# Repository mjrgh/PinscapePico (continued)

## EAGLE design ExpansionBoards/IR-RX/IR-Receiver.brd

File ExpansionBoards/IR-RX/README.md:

# IR Receiver Satellite Board for Pinscape Pico

This is a small satellite board for the Pinscape Pico expansion
boards (both the DIY-friendly and "Pro" boards), which hosts the IR
Receiver sensor that allows Pinscape to receive signals from IR remote
controls. 

The IR sensor is deliberately separated from the main board so that it
can be positioned where it can receive line-of-sight IR transmissions
from remote controls.  The main Pinscape boards are probably going to
be hidden inside your pinball cabinet, so it doesn't make sense to
position the IR receiver directly on those boards.  Instead, you'll
probably want to place the IR receiver somewhere either outside the
cabinet, or in an opening in the cabinet where it has a view of the
exterior.  For example, you could place it behind a small hole drilled
in your speaker panel, or in the front wall of the cabinet body.

There are two versions of the board: a DIY-friendly version that uses
through-hole parts, and a version using surface-mount parts.  The
versions are functionally identical, and both versions work with the
Pinscape DIY-Friendly and "Pro" SMD expansion boards.  All of them use
the same connectors.

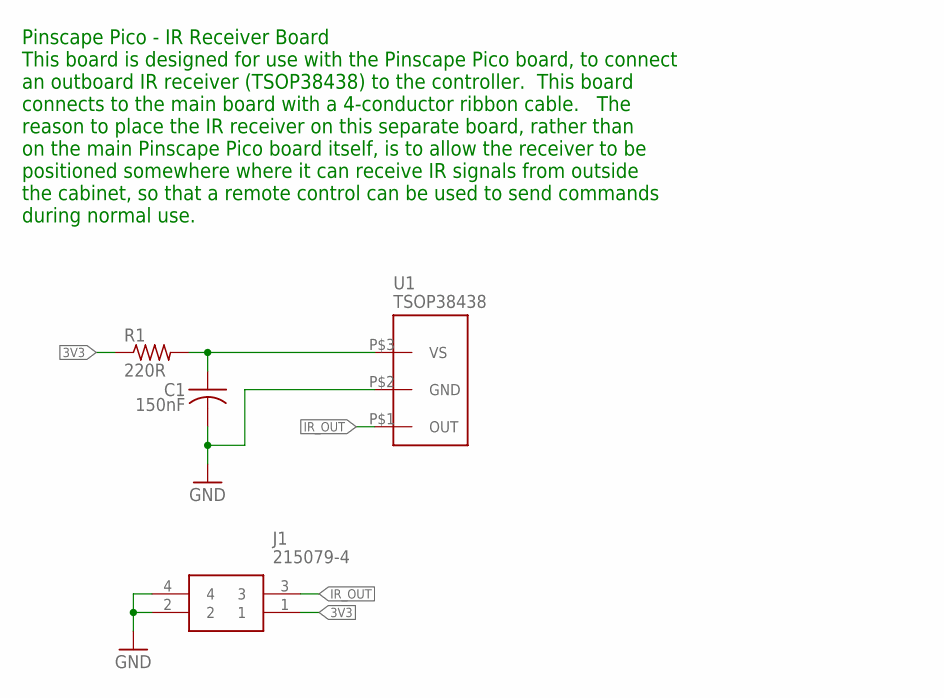
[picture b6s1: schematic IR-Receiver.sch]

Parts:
C1: 150nF; C025-040X050
J1: 215079-4; 2150794
R1: 220R; 0204/7; PARTNO 660-MS1/4DCT52R1002
U1: TSOP38438; TSOP382

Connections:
3V3: J1.1, R1.1
GND: C1.2, J1.2, J1.4, U1.P$2 (GND)
IR_OUT: J1.3, U1.P$1 (OUT)
unnamed: C1.1, R1.2, U1.P$3 (VS)

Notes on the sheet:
Pinscape Pico - IR Receiver Board This board is designed for use with the Pinscape Pico board, to connect an outboard IR receiver (TSOP38438) to the controller. This board connects to the main board with a 4-conductor ribbon cable. The reason to place the IR receiver on this separate board, rather 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

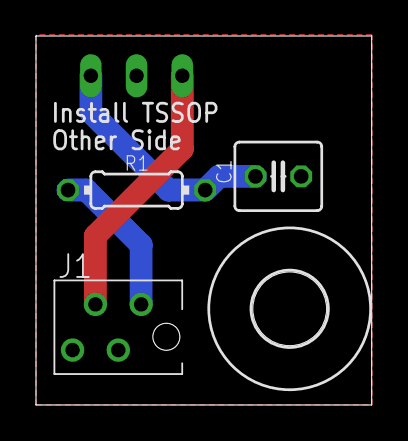
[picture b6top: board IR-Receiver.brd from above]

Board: 2 copper layers, 18.6 x 20.5 mm, 5 parts (1 on the bottom side), 4 nets.

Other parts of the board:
U$3: 4,1

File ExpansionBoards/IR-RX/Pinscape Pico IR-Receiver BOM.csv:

Qty,Value,Parts,Description,PARTNO,Comments
1,150nF,C1,"Capacitor, ceramic, 150nF, radial, 2.5mm lead pitch",K154K20X7RF53H5,
1,220R,R1,"Resistor, 200 Ohm, axial, 2mm 4 xmm",MFR25SFTF52-220R,
1,TSOP38438,U1,"IR receiver/demodulator, Vishay TSOP38438",TSOP38438,
1,MICROMATCH-4PIN,J1,"Connector, Micro-MaTch female-on-board, 4 pin, top entry",215079-4,
1,MICROMATCH-4PIN,PLUG_J1,"Plug for J1, Micro-MaTch male-on-wire, 4 pin, IDC",215083-4,

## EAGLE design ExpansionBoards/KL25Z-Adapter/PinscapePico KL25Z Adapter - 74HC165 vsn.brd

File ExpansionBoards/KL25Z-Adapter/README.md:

# Pinscape Pico - KL25Z adapter boards

These boards let you plug a Pico into your original-edition Pinscape
Expansion Boards for the KL25Z, with the Pico taking the place of the
KL25Z.  If you have a set of KL25Z expansion boards, this lets you
upgrade to the new Pinscape Pico software without changing all of your
other hardware.  It also lets you continue using the KL25Z expansion
boards even if your KL25Z is broken and you can't find a replacement.

The board works by routing pins on the KL25Z-style connectors to the
corresponding pins on the Pico - GPIO ports, power, ground, etc.
It also adds some extra hardware elements to fill in gaps in the
Pico's capabilities:

* A LI3DH accelerometer, to take the place of the KL25Z's built-in accelerometer

* GPIO expanders (PCA9555 or 74HC165, depending on the board version) to make
up the difference between the KL25Z's 50+ GPIO ports and the Pico's 26

* A high-quality 16-bit ADC (ADS1115), to supplement the Pico's low-resolution
on-board ADC (for smoother animation and better precision when using a
potentiometer-based plunger)

## Versions

The 74HC165-based version of the board is the official release.

The older PCA9555 version is also included for reference, but I'm not
planning to maintain it as an official release.  See notes on the
differences below.

## Credits

Thanks to Tengri (https://github.com/jueank) for the conversion to
through-hole sockets for the Pico.  The original design required
soldering the Pico directly to the board, which would make it nearly
impossible to replace the Pico if it ever failed.  Tengri's improved
design lets you use standard 20-position 0.1" socket headers, such as
Wurth 61302011821, that mate with 0.1" pin headers soldered to the
bottom of the Pico.  But you can also still solder the Pico directly
to the board if you prefer.

## Caveats

A few warnings about using the adapter boards:

* The adapter board **only** works with the original Pinscape KL25Z
expansion boards - and I'm talking very specifically about **my original three-board set**,
the one that's documented in the Pinscape Build Guide, with the 10x10cm
Main, Power, and Chime modules.  The adapter **doesn't**
turn the Pico into a general-purpose KL25Z emulator, and it probably
won't work with any third-party Pinscape boards (such as those from Oak
Micros or Arnoz), **unless** they use identical KL25Z pin assignments.
The obstacle to using the adapter with any other expansion boards or
add-on boards is that the adapter is completely inflexible about the KL25Z
pin assignments.  You can only use the adapter with an expansion board
that has exactly the same pin assignments as my original three-board set.
With a **real** KL25Z, it's possible to reconfigure the GPIO ports in
many different ways, which allowed people to design different expansion
board layouts.  The adapter board doesn't have that flexibility, so it
only works in the unique expansion board environment it was designed for.

* If you don't already have a set of the Pinscape KL25Z boards, you
should look at the new Pinscape Pico expansion boards instead.  Those
are designed from the ground up around the Pico, and they have some
improvements over the original KL25Z boards.

* The adapter **doesn't** make the Pico capable of running KL25Z
software.  You have to switch all of your software to the new Pinscape
Pico system.

* Pinscape Pico doesn't work with the Pinscape-for-KL25Z Config Tool,
so you'll also have to switch to the new Pinscape Pico version on the
Windows side.  You'll also have to tweak your DOF configuration to let
DOF know you're using the new system, and make sure you have the
latest DOF (which has support for Pinscape Pico built in), but
otherwise you shouldn't have to change anything in DOF or most other
client software.

* **DIYers beware!** These boards are designed with small-pitch SMD
(surface-mount) parts, which are difficult to solder by hand.  They're
really meant to be assembled by robots.  I didn't really have any
choice with this board because of the constraint that it has to fit
into the same physical space as an actual KL25Z, so that it can fit
into the space allowed in the expansion boards.  The equivalent
easy-to-solder "through-hole" parts are just too big to fit into such
a small space.  One thing you might look into is "PCBA" (PCB Assembly)
services, which are companies that both fabricate the circuit boards
and solder the parts for you.  This is more costly than doing it
yourself, and the ordering process can be intimidatingly complex,
but it might end up being easier than trying to do the soldering
by hand (and possibly cheaper, if you take into account the cost
of extra parts you might need to order for practice or re-dos.)

## Pinscape Pico Configuration

The project folder includes a JSON file for each adapter board layout
with the basic Pinscape Pico configuration for that board.  The two
boards require individual JSON configurations because of the different
hardware.  Import the JSON file matching your chosen board design into
the Config Editor in the Config Tool.

You'll have to do some additional hand-editing on the file because of
the modular design of the KL25Z expansion boards.  The KL25Z expansion
board system allows you to add zero or more "Power" and "Chime" boards
to the basic setup, so you have to set up the Pico configuration to
match the number of boards of each kind you have.  The JSON file has
comments explaining which sections will need your attention, so browse
through the file and follow the instructions you find.

In addition to customizing the configuration for your expansion board
hardware, you'll also want to go through the `button:` section to set
up your preferred button mappings, and arrange the `output:` section
so that the ports are arranged in the same order as your KL25Z setup.
Both systems let you assign DOF port numbers to the physical output
ports in any order.  It will make it easier to move your DOF configuration
to the new system if you replicate the same output port numbering that
you used in the KL25Z setup.

## DOF Setup

Even though Pinscape Pico shares a "brand name" with the original
KL25Z Pinscape, they're completely different systems.  That includes

at the DOF level - DOF thinks about them as unrelated boards, requiring
different communications protocols.  So you'll have to update your
DOF Config Tool settings to select the new boards.

Otherwise, the DOF setup should be the same as with the KL25Z boards.
Both systems let you map your physical output ports to any arrangement
of DOF port numbers, so the first thing you should probably do in the
Pinscape Pico Config Tool is go through the `outputs:` section and
make sure that the ports are all listed in the same order as in your
KL25Z setup.

## 74HC165 vs PCA9555 versions

The repository has two versions of the board: one based on the 74HC165
shift register chip, and one based on the PCA9555 I2C GPIO expander chip.

<b>The 74HC165 board is the official version.</b>  I don't plan to
maintain the PCA9555 version, but it's included for reference.

The difference between the two boards is the choice of chip used to
physically connect the button inputs to the Pico.  The older version
was based on the PCA9555 GPIO expander, which is designed to add
digital in/out ports equivalent to a microcontroller's native GPIO
ports, for applications such as this one where the microcontroller
doesn't have enough native ports to meet the application's
requirements.  In this case, we have a lot more button inputs than
the Pico has GPIO ports.  The newer version of the board accomplishes
the same thing using 74HC165 shift register chips.

The main advantage of the PCA9555 over the 74HC165, and the reason I
started with the PCA9555 version, is that the PCA9555 has built-in
pull-up resistors.  Regardless of which chip is used, each button
input requires a pull-up resistor, to give it a definite voltage
reading when the button isn't being pressed.  The PCA9555 happens to
include pull-up resistors internally on every port, which makes it
really easy to use for button inputs, since you don't need to add any
parts to get the required pull-up voltage.  The 74HC165, in contrast,
doesn't provide any equivalent, so you have to add one resistor per
button port - with 24 button ports on this board, that's 24 extra
parts.  So I initially designed the board around the PCA9555, for the
sake of reducing the parts cost and the assembly work.

But the PCA9555 has a major disadvantage, which is that it's not
nearly as fast as the 74HC165.  It can only sample the button inputs
about once per millisecond.  For most applications, that would be
fine, but it's a negative for a gaming device like this one, where
users desire extremely low latency for control inputs.  The 74HC165
solves this; it can clock samples into the host microcontroller at
megahertz speeds, allowing buttons to be sampled every 10 to 20
microseconds.  That's effectively zero latency.  I decided that the
fast sampling rate is important enough for a pin cab controller to
justify all of those extra resistors.

I'm keeping the PCA9555 board in the repository just in case anyone
deems the reduced parts cost more important than the reduced latency
of the 74HC165 version.  However, I haven't brought it up to date
with the changes for the through-hole pin sockets for the Pico, and
I don't plan to maintain it, since I think the 74HC165 version is
the better choice for most people.

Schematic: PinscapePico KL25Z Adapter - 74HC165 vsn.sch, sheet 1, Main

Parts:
FRDM1: KL25Z; FRDM_KL25Z_NORMAL
LED1: EC3528ARGB
R1, R2: 100R; R1206
R3: 300R; R1206
R6, R7: 4k; R1206
RASPBERRY_PI_PICO: RPI_PICO_NO_DEBUG; RPI_PICO_TH_NO_DEBUG
SW1: TS-1187A-B-A-B

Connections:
3V3_PICO: FRDM1.3V3 (IOREF/3V3), FRDM1.P3V3 (3V3), LED1.1, R6.1, R7.1, RASPBERRY_PI_PICO.3V3; also elsewhere on the board
5V_PICO: FRDM1.5V, RASPBERRY_PI_PICO.VBUS
ACCEL_INTR: RASPBERRY_PI_PICO.GP14; also elsewhere on the board
ADC_INTR: RASPBERRY_PI_PICO.GP7; also elsewhere on the board
BUTTON1: FRDM1.A4 (A4/PTC2); also elsewhere on the board
BUTTON2: FRDM1.A3 (A3/PTB3); also elsewhere on the board
BUTTON3: FRDM1.A2 (A2/PTB2); also elsewhere on the board
BUTTON4: FRDM1.A1 (A1/PTB1); also elsewhere on the board
BUTTON5: FRDM1.PTE30; also elsewhere on the board
BUTTON6: FRDM1.PTC11; also elsewhere on the board
BUTTON7: FRDM1.PTE5; also elsewhere on the board
BUTTON8: FRDM1.PTE4; also elsewhere on the board
BUTTON9: FRDM1.PTE3; also elsewhere on the board
BUTTON10: FRDM1.PTE2; also elsewhere on the board
BUTTON11: FRDM1.PTB11; also elsewhere on the board
BUTTON12: FRDM1.PTB10; also elsewhere on the board
BUTTON13: FRDM1.PTB9; also elsewhere on the board
BUTTON14: FRDM1.PTB8; also elsewhere on the board
BUTTON15: FRDM1.PTC12; also elsewhere on the board
BUTTON16: FRDM1.PTC13; also elsewhere on the board
BUTTON17: FRDM1.PTC16; also elsewhere on the board
BUTTON18: FRDM1.PTC17; also elsewhere on the board
BUTTON19: FRDM1.PTA16; also elsewhere on the board
BUTTON20: FRDM1.PTA17; also elsewhere on the board
BUTTON21: FRDM1.PTE31; also elsewhere on the board
BUTTON22: FRDM1.PTD6; also elsewhere on the board
BUTTON23: FRDM1.PTD7; also elsewhere on the board
BUTTON24: FRDM1.D15 (SCL/PTE1); also elsewhere on the board
BUTTON_CLK: RASPBERRY_PI_PICO.GP9; also elsewhere on the board
BUTTON_DATA: RASPBERRY_PI_PICO.GP12; also elsewhere on the board
BUTTON_SHLD: RASPBERRY_PI_PICO.GP8; also elsewhere on the board
CHIME_ENA: FRDM1.D2 (D2/PTD4); also elsewhere on the board
CHIME_LATCH: FRDM1.D3 (D3/PTA12), RASPBERRY_PI_PICO.GP2
CHIME_SCLK: FRDM1.D4 (D4/PTA4), RASPBERRY_PI_PICO.GP1
CHIME_SOUT: FRDM1.D5 (D5/PTA5), RASPBERRY_PI_PICO.GP3
EXPAN1: FRDM1.PTC4; also elsewhere on the board
EXPAN2: FRDM1.PTC3; also elsewhere on the board
EXPAN3: FRDM1.PTC0; also elsewhere on the board
EXPAN4: FRDM1.D1 (D1/PTA2); also elsewhere on the board
GND: FRDM1.GND0, FRDM1.GND1, FRDM1.GND2, RASPBERRY_PI_PICO.AGND, RASPBERRY_PI_PICO.GND@1 (GND), RASPBERRY_PI_PICO.GND@2 (GND), RASPBERRY_PI_PICO.GND@3 (GND), RASPBERRY_PI_PICO.GND@4 (GND), RASPBERRY_PI_PICO.GND@6 (GND), RASPBERRY_PI_PICO.GND@7 (GND), RASPBERRY_PI_PICO.GND@8 (GND), SW1.C, SW1.D; also elsewhere on the board
IR_IN: FRDM1.D8 (D8/PTA13), RASPBERRY_PI_PICO.GP6
IR_OUT: FRDM1.D7 (D7/PTC9), RASPBERRY_PI_PICO.GP0
KNOCKER: FRDM1.D6 (D6/PTC8); also elsewhere on the board
LED_B: R1.1, RASPBERRY_PI_PICO.GP22
LED_G: R2.1, RASPBERRY_PI_PICO.GP26_A0
LED_R: R3.1, RASPBERRY_PI_PICO.GP27_A1
unnamed: LED1.3, R3.2
unnamed: LED1.2, R1.2
unnamed: LED1.4, R2.2
PICO_RUN: RASPBERRY_PI_PICO.RUN, SW1.A, SW1.B
PLUNGER_ADC: FRDM1.A0 (A0/PTB0), RASPBERRY_PI_PICO.GP28_A2; also elsewhere on the board
PLUNGER_CAL_BTN: FRDM1.PTE29; also elsewhere on the board
PLUNGER_CAL_LED: FRDM1.PTE23; also elsewhere on the board
PLUNGER_IRQ1_SCL: FRDM1.D10 (D10/PTD0), FRDM1.PTE21, RASPBERRY_PI_PICO.GP11
PLUNGER_IRQ2: FRDM1.D9 (D9/PTD5), FRDM1.PTE22, RASPBERRY_PI_PICO.GP13
PLUNGER_SDA: FRDM1.PTE20, RASPBERRY_PI_PICO.GP10
PSU2_STATUS_SENSE: FRDM1.D11 (D11/PTD2), RASPBERRY_PI_PICO.GP20
PSU2_STATUS_SET: FRDM1.D14 (SDA/PTE0), RASPBERRY_PI_PICO.GP21
PWM_BLANK: FRDM1.PTC7, RASPBERRY_PI_PICO.GP18
PWM_GSCLK: FRDM1.D0 (D0/PTA1), RASPBERRY_PI_PICO.GP16
PWM_SCLK: FRDM1.PTC5, RASPBERRY_PI_PICO.GP15
PWM_SIN: FRDM1.PTC6, RASPBERRY_PI_PICO.GP17
PWM_XLAT: FRDM1.PTC10, RASPBERRY_PI_PICO.GP19
SCL: R7.2, RASPBERRY_PI_PICO.GP5; also elsewhere on the board
SDA: R6.2, RASPBERRY_PI_PICO.GP4; also elsewhere on the board
TV_RELAY: FRDM1.D12 (D12/PTD3); also elsewhere on the board

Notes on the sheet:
Button 29=TV SWITCH OUT
30 = KNOCKER TRIGGER
Pico Hard Reset
I2C Pullup
Install 0.1" pin headers on BOTTOM of board to mate with expansion board KL25Z sockets
RGB Status LED
Install 0.1" pin sockets on top of board to mate with 0.1" headers on bottom of Pico
KL25Z Compatible Connectors
NOTE: DO NOT INSTALL A KL25Z HERE! This whole board TAKES THE PLACE of a KL25Z. It DOESN'T connect to an actual KL25Z.

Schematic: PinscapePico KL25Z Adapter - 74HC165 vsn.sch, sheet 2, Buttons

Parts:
C1, C2, C3: 0.1uF; C1206
IC1, IC2, IC3: SN74HC165DR; SOIC127P600X175-16N
RN1, RN2, RN3, RN4, RN6, RN8: CTS742C083

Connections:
3V3_PICO: C1.1, C2.1, C3.1, IC1.16 (VCC), IC2.16 (VCC), IC3.16 (VCC), RN1.5, RN1.6, RN1.7, RN1.8, RN2.5, RN2.6, RN2.7, RN2.8, RN3.5, RN3.6, RN3.7, RN3.8, RN4.1, RN4.2, RN4.3, RN4.4, RN6.1, RN6.2, RN6.3, RN6.4, RN8.1, RN8.2, RN8.3, RN8.4; also elsewhere on the board
BUTTON1: IC1.11 (A), RN3.4; also elsewhere on the board
BUTTON2: IC1.5 (G), RN8.6; also elsewhere on the board
BUTTON3: IC1.12 (B), RN3.3; also elsewhere on the board
BUTTON4: IC1.4 (F), RN8.7; also elsewhere on the board
BUTTON5: IC1.6 (H), RN8.5; also elsewhere on the board
BUTTON6: IC1.14 (D), RN3.1; also elsewhere on the board
BUTTON7: IC1.13 (C), RN3.2; also elsewhere on the board
BUTTON8: IC1.3 (E), RN8.8; also elsewhere on the board
BUTTON9: IC2.6 (H), RN6.5; also elsewhere on the board
BUTTON10: IC2.11 (A), RN2.4; also elsewhere on the board
BUTTON11: IC2.12 (B), RN2.3; also elsewhere on the board
BUTTON12: IC2.4 (F), RN6.7; also elsewhere on the board
BUTTON13: IC2.13 (C), RN2.2; also elsewhere on the board
BUTTON14: IC2.5 (G), RN6.6; also elsewhere on the board
BUTTON15: IC2.14 (D), RN2.1; also elsewhere on the board
BUTTON16: IC2.3 (E), RN6.8; also elsewhere on the board
BUTTON17: IC3.11 (A), RN1.4; also elsewhere on the board
BUTTON18: IC3.12 (B), RN1.3; also elsewhere on the board
BUTTON19: IC3.13 (C), RN1.2; also elsewhere on the board
BUTTON20: IC3.14 (D), RN1.1; also elsewhere on the board
BUTTON21: IC3.3 (E), RN4.8; also elsewhere on the board
BUTTON22: IC3.4 (F), RN4.7; also elsewhere on the board
BUTTON23: IC3.5 (G), RN4.6; also elsewhere on the board
BUTTON24: IC3.6 (H), RN4.5; also elsewhere on the board
BUTTON_CLK: IC1.2 (CLK), IC2.2 (CLK), IC3.2 (CLK); also elsewhere on the board
BUTTON_DATA: IC1.9 (QH); also elsewhere on the board
BUTTON_SHLD: IC1.1 (SH/!LD), IC2.1 (SH/!LD), IC3.1 (SH/!LD); also elsewhere on the board
GND: C1.2, C2.2, C3.2, IC1.8 (GND), IC1.15 (CLK_INH), IC2.8 (GND), IC2.15 (CLK_INH), IC3.8 (GND), IC3.10 (SER), IC3.15 (CLK_INH); also elsewhere on the board
unnamed: IC1.10 (SER), IC2.9 (QH)
unnamed: IC2.10 (SER), IC3.9 (QH)

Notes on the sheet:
Button Port Pull-ups
Button Input Shift Registers

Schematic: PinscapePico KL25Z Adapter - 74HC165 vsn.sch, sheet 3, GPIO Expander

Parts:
C6: 0.1uF; C1206
IC6: PCA9555APW,118; SOP65P640X110-24N

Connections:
3V3_PICO: C6.1, IC6.24 (VDD); also elsewhere on the board
CHIME_ENA: IC6.7 (P0_3); also elsewhere on the board
EXPAN1: IC6.8 (P0_4); also elsewhere on the board
EXPAN2: IC6.6 (P0_2); also elsewhere on the board
EXPAN3: IC6.4 (P0_0); also elsewhere on the board
EXPAN4: IC6.5 (P0_1); also elsewhere on the board
GND: C6.2, IC6.2 (A1), IC6.3 (A2), IC6.12 (VSS), IC6.21 (A0); also elsewhere on the board
KNOCKER: IC6.9 (P0_5); also elsewhere on the board
PLUNGER_CAL_BTN: IC6.15 (P1_2); also elsewhere on the board
PLUNGER_CAL_LED: IC6.14 (1_1); also elsewhere on the board
SCL: IC6.22 (SCL); also elsewhere on the board
SDA: IC6.23 (SDA); also elsewhere on the board
TV_RELAY: IC6.11 (P0_7); also elsewhere on the board

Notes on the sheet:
I2C Address 0x20 (010 0000)

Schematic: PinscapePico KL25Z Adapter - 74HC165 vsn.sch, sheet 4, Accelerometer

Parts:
C4: 0.1uF; C1206
IC4: LIS3DHTR

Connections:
3V3_PICO: C4.1, IC4.1 (VDDIO), IC4.8 (CS), IC4.14 (VDD); also elsewhere on the board
ACCEL_INTR: IC4.11 (INT1); also elsewhere on the board
GND: C4.2, IC4.5 (GND_1), IC4.7 (SDO/SA0), IC4.10 (RES), IC4.12 (GND_2), IC4.13 (ADC3), IC4.15 (ADC2), IC4.16 (ADC1); also elsewhere on the board
SCL: IC4.4 (SCL/SPC); also elsewhere on the board
SDA: IC4.6 (SDA/SDI/SDO); also elsewhere on the board

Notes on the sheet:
Accelerometer - LIS3DH I2C address 0x18 (001 1000)
SDO/SA0 sets I2C address: GND = 0x18, VDD = 0x19
CS = VDD -> I2C mode
Note: also pin-compatible with LIS3DSH (address 0x1E, 001 1110)

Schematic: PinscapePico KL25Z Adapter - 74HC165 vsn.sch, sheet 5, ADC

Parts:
C5: 0.1uF; C1206
IC5: ADS1115IDGSR; SOP50P490X110-10N
R4, R5: 10K; R1206

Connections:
3V3_PICO: C5.1, IC5.8 (VDD), R5.1; also elsewhere on the board
ADC_INTR: IC5.2 (ALERT/RDY); also elsewhere on the board
GND: C5.2, IC5.1 (ADDR), IC5.3 (GND), R4.1; also elsewhere on the board
unnamed: IC5.7 (AIN3), R4.2, R5.2
PLUNGER_ADC: IC5.4 (AIN0); also elsewhere on the board
SCL: IC5.10 (SCL); also elsewhere on the board
SDA: IC5.9 (SDA); also elsewhere on the board

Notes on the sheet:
I2C Bus Address 0x48 (100 1000)
Plunger ADC The Pico has an on-board ADC, but its resolution is fairly coarse (effectively 8 bits), and it has some well-known defects that were only discovered after production started. Potentiometer plungers in particular can benefit from a better ADC, and are probably the most popular plunger se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

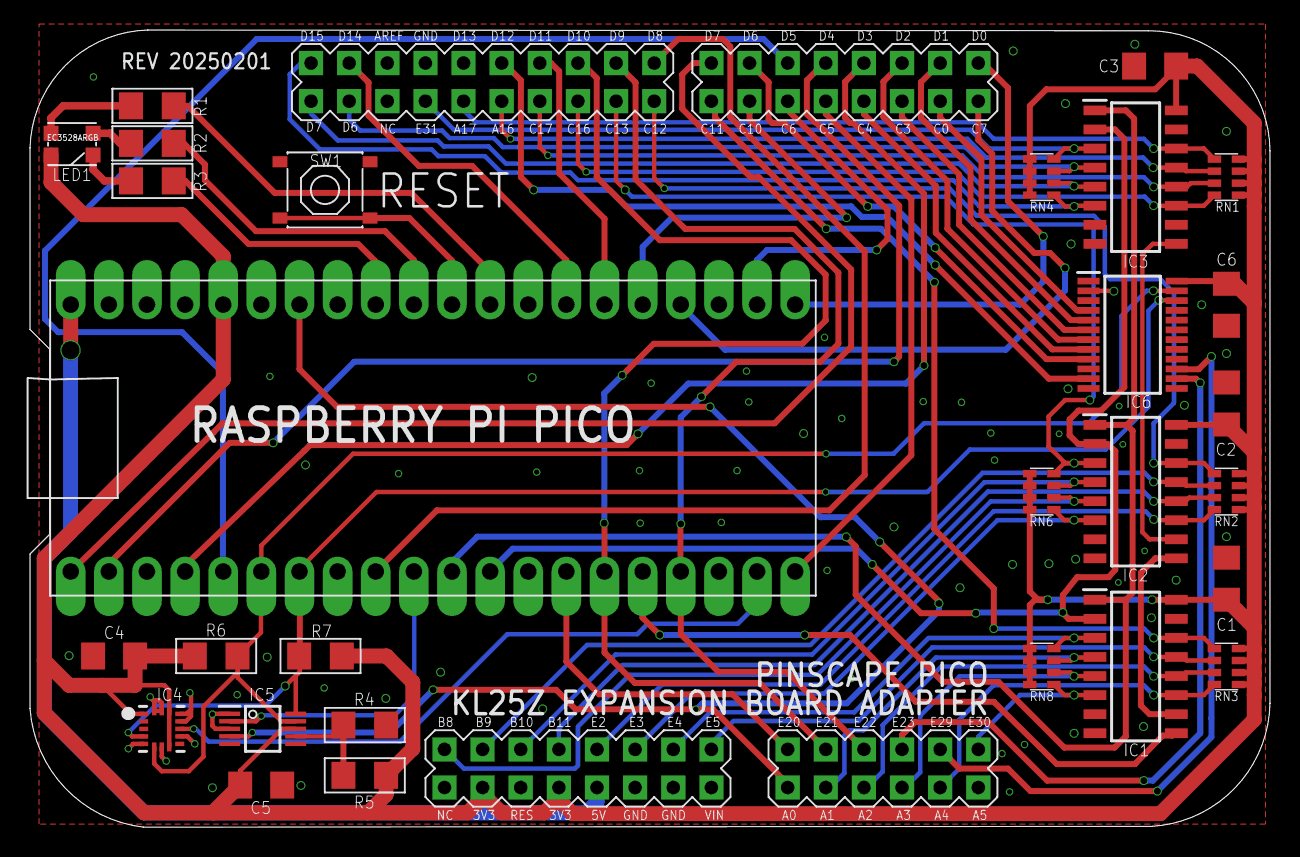
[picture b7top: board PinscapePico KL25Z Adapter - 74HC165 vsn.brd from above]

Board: 2 copper layers, 82.6 x 53.1 mm, 29 parts (0 on the bottom side), 69 nets.

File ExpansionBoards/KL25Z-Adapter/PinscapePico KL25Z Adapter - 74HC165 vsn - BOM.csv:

Qty,Value,Parts,Description,PARTNO,Comments
1,Pico-H,RASPBERRY_PI_PICO,Raspberry Pi Pico w/pin headers installed,SC0917,
2,"0.1"" SOCK-HD 1X20",RASPBERRY_PI_PICO,"Socket Header, 20 position, 2.54mm pitch",61302011821,
6,0.1uF,"C1, C2, C3, C4, C5, C6","Capacitor, 0.1uF, ceramic, SMD 1206",1206B104K500CT,
2,100R,"R1, R2","Resistor, 100 Ohm, SMD 1206",RK73H2BTTDD1000F,
2,10K,"R4, R5","Resistor, 10K, SMD 1206",CR1206-JW-103ELF,
1,300R,R3,"Resistor, 300 Ohm, SMD 1206",CR1206-JW-301ELF,
2,4k,"R6, R7","Resistor, 4K, SMD 1206",RN73R2BTTD4001B25,
1,ADS1115IDGSR,IC5,"16-Bit 860SPS 4-Ch Delta-Sigma ADC With PGA, Oscillator, Vref, Comparator, and I2C",595-ADS1115IDGSR,
6,10K 4POS,"RN1, RN2, RN3, RN4, RN6, RN8","Chip Resistor Array 4 Single Resistor, 10K, SMD 0603 x 4",WA06X103JTL,Substitute: 742C083103JP
1,RGB,LED1,"RGB LED, 5mA, common anode, SMD 3528 package",150141M173100,
1,"0.1"" SOCK-HD 2x6",FRDM1,"Socket header, 0.1"" pitch, 2x6 position",61301221821,FRDM-KL25Z header socket
2,"0.1"" SOCK-HD 2x8",FRDM1,"Socket header, 0.1"" pitch, 2x8 position",61301621821,FRDM-KL25Z header socket
1,"0.1"" SOCK-HD 2x10",FRDM1,"Socket header, 0.1"" pitch, 2x10 position",61302021821,FRDM-KL25Z header socket
1,LIS3DHTR,IC4,"Accelerometer 3-Axis 2g/16g 1.8V LGA16 STMicroelectronics LIS3DHTR Accelerometer IC, 3-axis, I2C, SPI 1.71  3.6 V, 16-Pin LGA",511-LIS3DHTR,
1,"PCA9555APW,118",IC6,"NXP - PCA9555APW,118 - I/O EXPANDER, 16BIT, 400KHZ, TSSOP-24",771-PCA9555APW118,
3,SN74HC165DR,"IC1, IC2, IC3",8-Bit Parallel-Load Shift Registers,595-SN74HC165DR,
1,TS-1187A-B-A-B,SW1,"Pushbutton switch, SPST, SMD",TS18-5-25-SL-260-SMT-TR,
,,,,,
,,,,,
,,,,,
,,,,,
,,,,,
,,,,,
,,,,,
,,,,,

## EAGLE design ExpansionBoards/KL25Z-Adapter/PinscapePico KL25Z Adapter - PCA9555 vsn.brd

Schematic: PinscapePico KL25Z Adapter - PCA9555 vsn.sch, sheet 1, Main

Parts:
FRDM1: KL25Z; FRDM_KL25Z_NORMAL
LED1: EC3528ARGB
R1, R2: 100R; R1206
R3: 300R; R1206
R6, R7: 4K; R1206
RASPBERRY_PI_PICO: RPI_PICO_NO_DEBUG; RPI_PICO_TH_NO_DEBUG
SW1: TS-1187A-B-A-B

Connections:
3V3_PICO: FRDM1.3V3 (IOREF/3V3), FRDM1.P3V3 (3V3), LED1.1, R6.1, R7.1, RASPBERRY_PI_PICO.3V3; also elsewhere on the board
5V_PICO: FRDM1.5V, RASPBERRY_PI_PICO.VBUS
ACCEL_INTR: RASPBERRY_PI_PICO.GP14; also elsewhere on the board
ADC_INTR: RASPBERRY_PI_PICO.GP7; also elsewhere on the board
BUTTON1: FRDM1.A4 (A4/PTC2), RASPBERRY_PI_PICO.GP8
BUTTON2: FRDM1.A3 (A3/PTB3), RASPBERRY_PI_PICO.GP9
BUTTON3: FRDM1.A2 (A2/PTB2), RASPBERRY_PI_PICO.GP21
BUTTON4: FRDM1.A1 (A1/PTB1), RASPBERRY_PI_PICO.GP20
BUTTON5: FRDM1.PTE30; also elsewhere on the board
BUTTON6: FRDM1.PTC11; also elsewhere on the board
BUTTON7: FRDM1.PTE5; also elsewhere on the board
BUTTON8: FRDM1.PTE4; also elsewhere on the board
BUTTON9: FRDM1.PTE3; also elsewhere on the board
BUTTON10: FRDM1.PTE2; also elsewhere on the board
BUTTON11: FRDM1.PTB11; also elsewhere on the board
BUTTON12: FRDM1.PTB10; also elsewhere on the board
BUTTON13: FRDM1.PTB9; also elsewhere on the board
BUTTON14: FRDM1.PTB8; also elsewhere on the board
BUTTON15: FRDM1.PTC12; also elsewhere on the board
BUTTON16: FRDM1.PTC13; also elsewhere on the board
BUTTON17: FRDM1.PTC16; also elsewhere on the board
BUTTON18: FRDM1.PTC17; also elsewhere on the board
BUTTON19: FRDM1.PTA16; also elsewhere on the board
BUTTON20: FRDM1.PTA17; also elsewhere on the board
BUTTON21: FRDM1.PTE31; also elsewhere on the board
BUTTON22: FRDM1.PTD6; also elsewhere on the board
BUTTON23: FRDM1.PTD7; also elsewhere on the board
BUTTON24: FRDM1.D15 (SCL/PTE1); also elsewhere on the board
BUTTON_INTR: RASPBERRY_PI_PICO.GP12; also elsewhere on the board
CHIME_ENA: FRDM1.D2 (D2/PTD4); also elsewhere on the board
CHIME_LATCH: FRDM1.D3 (D3/PTA12), RASPBERRY_PI_PICO.GP2
CHIME_SCLK: FRDM1.D4 (D4/PTA4), RASPBERRY_PI_PICO.GP1
CHIME_SOUT: FRDM1.D5 (D5/PTA5), RASPBERRY_PI_PICO.GP3
EXPAN1: FRDM1.PTC4; also elsewhere on the board
EXPAN2: FRDM1.PTC3; also elsewhere on the board
EXPAN3: FRDM1.PTC0; also elsewhere on the board
EXPAN4: FRDM1.D1 (D1/PTA2); also elsewhere on the board
GND: FRDM1.GND0, FRDM1.GND1, FRDM1.GND2, RASPBERRY_PI_PICO.AGND, RASPBERRY_PI_PICO.GND@1 (GND), RASPBERRY_PI_PICO.GND@2 (GND), RASPBERRY_PI_PICO.GND@3 (GND), RASPBERRY_PI_PICO.GND@4 (GND), RASPBERRY_PI_PICO.GND@6 (GND), RASPBERRY_PI_PICO.GND@7 (GND), RASPBERRY_PI_PICO.GND@8 (GND), SW1.C, SW1.D; also elsewhere on the board
IR_IN: FRDM1.D8 (D8/PTA13), RASPBERRY_PI_PICO.GP6
IR_OUT: FRDM1.D7 (D7/PTC9), RASPBERRY_PI_PICO.GP0
KNOCKER: FRDM1.D6 (D6/PTC8); also elsewhere on the board
LED_B: R1.1, RASPBERRY_PI_PICO.GP22
LED_G: R2.1, RASPBERRY_PI_PICO.GP26_A0
LED_R: R3.1, RASPBERRY_PI_PICO.GP27_A1
unnamed: LED1.3, R3.2
unnamed: LED1.2, R1.2
unnamed: LED1.4, R2.2
PICO_RUN: RASPBERRY_PI_PICO.RUN, SW1.A, SW1.B
PLUNGER_ADC: FRDM1.A0 (A0/PTB0), RASPBERRY_PI_PICO.GP28_A2; also elsewhere on the board
PLUNGER_CAL_BTN: FRDM1.PTE29; also elsewhere on the board
PLUNGER_CAL_LED: FRDM1.PTE23; also elsewhere on the board
PLUNGER_IRQ1_SCL: FRDM1.D10 (D10/PTD0), FRDM1.PTE21, RASPBERRY_PI_PICO.GP11
PLUNGER_IRQ2: FRDM1.D9 (D9/PTD5), FRDM1.PTE22, RASPBERRY_PI_PICO.GP13
PLUNGER_SDA: FRDM1.PTE20, RASPBERRY_PI_PICO.GP10
PSU2_STATUS_SENSE: FRDM1.D11 (D11/PTD2); also elsewhere on the board
PSU2_STATUS_SET: FRDM1.D14 (SDA/PTE0); also elsewhere on the board
PWM_BLANK: FRDM1.PTC7, RASPBERRY_PI_PICO.GP18
PWM_GSCLK: FRDM1.D0 (D0/PTA1), RASPBERRY_PI_PICO.GP16
PWM_SCLK: FRDM1.PTC5, RASPBERRY_PI_PICO.GP15
PWM_SIN: FRDM1.PTC6, RASPBERRY_PI_PICO.GP17
PWM_XLAT: FRDM1.PTC10, RASPBERRY_PI_PICO.GP19
SCL: R7.2, RASPBERRY_PI_PICO.GP5; also elsewhere on the board
SDA: R6.2, RASPBERRY_PI_PICO.GP4; also elsewhere on the board
TV_RELAY: FRDM1.D12 (D12/PTD3); also elsewhere on the board

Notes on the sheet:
Button 29=TV SWITCH OUT
30 = KNOCKER TRIGGER
Pico Hard Reset
I2C Pull-ups
KL25Z Header Connectors Install 0.1" pin sockets on BOTTOM of board

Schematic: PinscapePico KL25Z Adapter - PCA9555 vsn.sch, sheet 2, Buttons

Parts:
C1, C2: 0.1uF; C1206
IC1, IC2: PCA9555APW,118; SOP65P640X110-24N

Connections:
3V3_PICO: C1.1, C2.1, IC1.24 (VDD), IC2.21 (A0), IC2.24 (VDD); also elsewhere on the board
BUTTON5: IC1.16 (P1_3); also elsewhere on the board
BUTTON6: IC1.15 (P1_2); also elsewhere on the board
BUTTON7: IC1.14 (1_1); also elsewhere on the board
BUTTON8: IC1.13 (P1_0); also elsewhere on the board
BUTTON9: IC1.11 (P0_7); also elsewhere on the board
BUTTON10: IC1.10 (P0_6); also elsewhere on the board
BUTTON11: IC1.9 (P0_5); also elsewhere on the board
BUTTON12: IC1.8 (P0_4); also elsewhere on the board
BUTTON13: IC1.7 (P0_3); also elsewhere on the board
BUTTON14: IC1.6 (P0_2); also elsewhere on the board
BUTTON15: IC1.5 (P0_1); also elsewhere on the board
BUTTON16: IC1.4 (P0_0); also elsewhere on the board
BUTTON17: IC2.13 (P1_0); also elsewhere on the board
BUTTON18: IC2.14 (1_1); also elsewhere on the board
BUTTON19: IC2.15 (P1_2); also elsewhere on the board
BUTTON20: IC2.16 (P1_3); also elsewhere on the board
BUTTON21: IC2.17 (P1_4); also elsewhere on the board
BUTTON22: IC2.18 (P1_5); also elsewhere on the board
BUTTON23: IC2.19 (P1_6); also elsewhere on the board
BUTTON24: IC2.20 (P1_7); also elsewhere on the board
BUTTON_INTR: IC1.1 (!INT), IC2.1 (!INT); also elsewhere on the board
CHIME_ENA: IC1.18 (P1_5); also elsewhere on the board
EXPAN1: IC2.11 (P0_7); also elsewhere on the board
EXPAN2: IC2.10 (P0_6); also elsewhere on the board
EXPAN3: IC2.9 (P0_5); also elsewhere on the board
EXPAN4: IC2.8 (P0_4); also elsewhere on the board
GND: C1.2, C2.2, IC1.2 (A1), IC1.3 (A2), IC1.12 (VSS), IC1.21 (A0), IC2.2 (A1), IC2.3 (A2), IC2.12 (VSS); also elsewhere on the board
KNOCKER: IC2.6 (P0_2); also elsewhere on the board
PLUNGER_CAL_BTN: IC2.4 (P0_0); also elsewhere on the board
PLUNGER_CAL_LED: IC2.5 (P0_1); also elsewhere on the board
PSU2_STATUS_SENSE: IC1.20 (P1_7); also elsewhere on the board
PSU2_STATUS_SET: IC1.19 (P1_6); also elsewhere on the board
SCL: IC1.22 (SCL), IC2.22 (SCL); also elsewhere on the board
SDA: IC1.23 (SDA), IC2.23 (SDA); also elsewhere on the board
TV_RELAY: IC2.7 (P0_3); also elsewhere on the board

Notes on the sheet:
I2C Address 0x20 (010 0000)
I2C Address 0x21 (010 0001)
All buttons are individual grounded inputs. Configure PCA9555 ports as inputs with internal pull-up resistors. A button input with an open switch reads as high (due to the internal pull-up); a closed switch reads as low (the switch connects the input to GND).

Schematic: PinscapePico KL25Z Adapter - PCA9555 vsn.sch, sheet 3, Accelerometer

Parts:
C3: 0.1uF; C1206
IC3: LIS3DHTR

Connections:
3V3_PICO: C3.1, IC3.1 (VDDIO), IC3.8 (CS), IC3.14 (VDD); also elsewhere on the board
ACCEL_INTR: IC3.11 (INT1); also elsewhere on the board
GND: C3.2, IC3.5 (GND_1), IC3.7 (SDO/SA0), IC3.10 (RES), IC3.12 (GND_2); also elsewhere on the board
SCL: IC3.4 (SCL/SPC); also elsewhere on the board
SDA: IC3.6 (SDA/SDI/SDO); also elsewhere on the board

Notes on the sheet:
Accelerometer I2C address 0x18 (001 1000)
SDO/SA0 sets I2C address: GND = 0x18, VDD = 0x19
CS = VDD -> I2C mode

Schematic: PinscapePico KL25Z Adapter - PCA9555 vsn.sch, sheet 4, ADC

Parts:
C4: 0.1uF; C1206
IC30: ADS1115IDGSR; SOP50P490X110-10N
R4, R5: 10K; R1206

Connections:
3V3_PICO: C4.1, IC30.8 (VDD), R5.1; also elsewhere on the board
ADC_INTR: IC30.2 (ALERT/RDY); also elsewhere on the board
GND: C4.2, IC30.1 (ADDR), IC30.3 (GND), R4.1; also elsewhere on the board
unnamed: IC30.7 (AIN3), R4.2, R5.2
PLUNGER_ADC: IC30.4 (AIN0); also elsewhere on the board
SCL: IC30.10 (SCL); also elsewhere on the board
SDA: IC30.9 (SDA); also elsewhere on the board

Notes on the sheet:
I2C Bus Address 0x48 (100 1000)
Plunger ADC The Pico has an on-board ADC, but its resolution is fairly coarse (effectively 8 bits), and it has some well-known defects that were only discovered after production started. Potentiometer plungers in particular can benefit from a better ADC, and are probably the most popular plunger se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

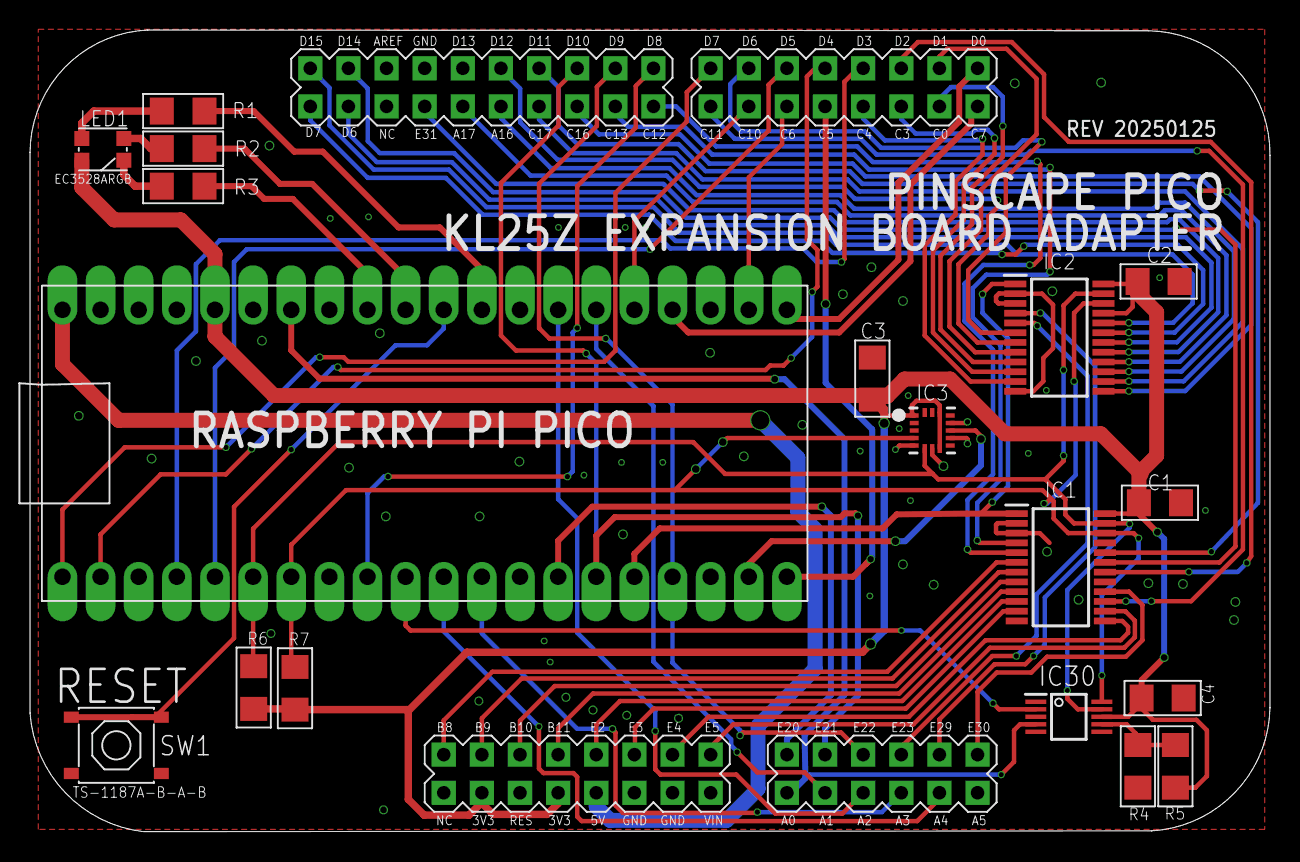
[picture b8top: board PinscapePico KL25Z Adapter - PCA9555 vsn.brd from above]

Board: 2 copper layers, 82.6 x 53.4 mm, 19 parts (0 on the bottom side), 65 nets.

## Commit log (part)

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2025-01-04 gitattributes correction
2025-01-05 link fix
2025-01-05 clean up generated/object files that shouldn't have been included
2025-01-05 more readme's
2025-01-05 release updates
2025-01-05 more images
2025-01-05 board notes
2025-01-08 readme tweaks
2025-01-10 add logo image
2025-01-11 fix TinyUSB 0.17.0 regression (vendord_reset error; broken USB connection on sleep/resume)
2025-01-11 readme updaets
2025-01-11 add a common project-wide version number
2025-01-11 readme edits
2025-01-20 v0.1.2 release
2025-01-25 KL25Z adapter board updates;
2025-01-25 KL25Z adapter readme edits
2025-01-27 Update Pro expansion board to use 74HC165 for all button inputs
2025-01-30 minor board updates
2025-01-30 number formatter fix
2025-01-30 Remove pull-up to primary Pico 3V3 on aux Pico reset
2025-01-31 DIY board: individual reset buttons per Pico; swap cross-board connectors
2025-02-01 fix lis3dh address in exp board config templates; CDC IN stall detection updates
2025-02-02 KL25Z adapters - connect AGND to GND
2025-02-02 Add SMD-socketed-Pico version of DIY Friendly boards
2025-02-03 Change to socketed Picos on DIY-friendly boards
2025-02-03 add main expansion board folder readme
2025-02-05 change to socketed Pico for Pro board
2025-02-06 Add connector board plan for Button Latency Tester II
2025-02-07 typo
2025-02-07 Remove double word in README.md
2025-02-07 add more chip wiring diagrams to JSON config doc; readme edits
2025-02-08 move old expansion boards into 'deprecated' subfolders'
2025-02-09 Add output port names to GUI Config Tool device overview pinout diagram
2025-02-10 Open Pinball Device library doc updates for Raw Input interface; readme edits
2025-02-10 Update Pro and KL25Z adapter boards to make LIS3DH footprint compatible with LIS3DSH
2025-02-11 add provisional support for TLC5947 (untested)
2025-02-11 improved TLC5940 PIO program
2025-02-12 OpenPinballDeviceLib - add friendly device name for UI displays based on special device recognition when possible
2025-02-13 fix crash when I2Cn is enabled with zero devices configured on bus
2025-02-13 Add TLC5947 to JSON config doc
2025-02-13 JSON config ref edits
2025-02-13 Add pca9555.initialOut to config doc/schema (#17)
2025-02-16 add protocol-level LedWiz emulation option
2025-02-16 Config Tool device search changes (related to LedWiz protocol addition, for less dependence on Feedback Controller ifc)
2025-02-17 v0.1.3
2025-02-18 v0.1.4
2025-02-19 fix possible race condition in 74hc165 startup
2025-02-19 v0.1.5
2025-02-21 Remove MSVC-redist dependency from Scintilla build
2025-02-24 Fix OutputManager::Set() port limit test
2025-02-25 add parts list (BOM) for Button Latency Tester II board
2025-02-26 Add flasher panel board design
2025-02-28 hard fault logging, preserve tail end of log across reset
2025-02-28 reduce JSON memory footprint
2025-03-01 v0.1.7
2025-03-05 BOM tweaks
2025-03-08 Open Pinball Device doc: add illustration for flipper switch layout
2025-03-10 PWMWorker: set fast slew rate and high drive strength on output ports
2025-03-11 Exp boards: update gate resistors in BOMs
2025-03-14 readme: add sample configurations
2025-03-14 exp board: IR RX: BOM correction
2025-03-14 exp board: pro: change battery holder to top clip type
2025-03-17 exp board: diy power: include old and new battery holders in BOM
2025-03-18 VCNL4010: add startup wait
2025-03-19 exp board: flasher panel: correct BOM line item for IDC housing
2025-03-19 exp board: DIY main: correct BOM line item for 3P pin strip
2025-03-22 exp board: flasher panel: add Amazon ASINs for equivalent LEDs
2025-03-22 exp board: power distro: BOM correction
2025-03-23 exp board: power distro: add relay coil diode
2025-03-23 exp board: power distro: change coin door interlock to AC
2025-03-25 fix i2cX command crash when bus is configured but not enabled
2025-03-25 fix UART GP initialization
2025-03-25 config tool: fix keyboard status refresh in button tester window on app bg/fg switching
2025-03-25 config ref help: add warning about connecting high-power devices to GPIOs
2025-03-25 PWMWorker data sheet edits
2025-03-26 exp board: power: change RTC power source to main Pico bus power
2025-03-26 fix UART logger config message
2025-03-26 config template fix for DIY main
2025-03-26 exp board: flasher panel: change header silkscreen markings for 16-pin connector orientation to match original KL25Z expansion boards
2025-03-26 exp board: DIY main: change recommended IR LED to new part in BOM
2025-03-27 exp board: DIY power: add guard ring and isolated ground plane under DS1307 crystal per App Note 58
2025-03-27 Fix error in pwm device command parsing
2025-03-27 fix CountPorts counting error in several devices
2025-03-30 exp board: power distro board tweaks
2025-04-01 tweaks to improve I2C latencies
2025-04-01 exp board: power distro: add clarification about 240VAC mains to readme
2025-04-04 document TLC5947 output port setup
2025-04-05 add 8-way gamepad hat switch
2025-04-05 comments
2025-04-07 add 'Pico Reboot' initial state for TV ON, remove button-style debouncing on inputs
2025-04-08 ConfigDocParser: strip HTML from summary text
2025-04-08 un-ignore pico_sdk_import.cmake in firmware .gitinclude's
2025-04-08 add I2C bus scan to Config Tool
2025-04-08 add LIS3DH setup guide
2025-04-09 fix I2C START/STOP condition sequencing in bus-clear operation (caused problems for LIS3DH)
2025-04-09 add gamepad hat switch
2025-04-09 v0.1.11
2025-04-10 LIS3DH guide edits; change keyboard rollover log message to debug status
2025-04-20 i2c: don't invoke IRQ completion callback on abort
2025-04-21 add scrollbar to nudge window
2025-04-21 v0.1.12
2025-04-23 exp board: power distro BOM correctin
2025-04-29 exp board readme edits
2025-05-02 exp board: DIY main: BOM correction
2025-05-28 add Pico2 RP2350 build
2025-05-28 mention Pico2 in readme
2025-06-04 Add provisional MMA8451Q support (not yet tested)
2025-06-07 exp board: update BOM for MOSFET recommendations
2025-06-21 exp boards: diy: add workaround photos for errata
2025-06-24 output port share groups
2025-06-25 readme edit (clarify that W is not supported)
2025-06-26 v0.1.15
2025-07-01 shared output devices: multiple share groups per device and per DOF port, pulsed ports; MMA8451Q setup notes
2025-07-01 MMA8451Q guide edits
2025-07-01 PWMWorker data sheet: clarify that initial OUTn port state is high-value pull-down
2025-08-02 make PWMWorker startup timeout configurable; add outputs[].enableSourceDuringSuspend
2025-08-08 MMA8415Q: fix parsing for poll mode (no 'interrupt:' entry)
2025-08-10 v0.1.17
2025-08-16 add link to Build Guide chapter on board fabrication to exp board readme
2025-08-16 ADC based button source
2025-08-29 mma8451q: add WHO_AM_I recognition for mma8452q (which seems to function correctly with existing driver)
2025-09-10 move ADC config key enumeration to ADCManager
2025-09-11 fix command-line config tool IR TX (--ir-send); fix Pico crash sending IR command when IR TX not configured
2025-09-12 add Open Pinball Device tester configuration
2025-09-12 oops, really add the OPD tester
2025-09-17 Trivial fix for the mma8451q JSON example
2025-09-23 fix initial state for toggle buttons when underlying soruce is active-low (discussion #71)
2025-10-11 Fix .pio assembly under UNIX
2025-10-13 Exp boards: DIY: add notes on BOM versions
2025-10-14 exp boards: power distro: add pin labels for 120VAC headers
2025-10-14 button type:'reset' action: add Safe and Factory mode options
2025-10-14 code comments
2025-10-18 add gpio() USB logical axis source, for direct digital GPIO sampling
2025-10-18 Change 'set to -1 if not connected' in config template comments to 'omit if not connected'
2025-10-21 Improve expansion board IR receiver documentation
2025-10-23 gcc 14.3 updates for ButtonLatencyTester2; remove some generated sdk files from repos
2025-10-23 Pico2 build correction
2025-10-28 config starter template comment edits
2025-11-29 JSON config ref correction (#88)
2025-12-07 exp board BOMs: change to original manufacturer part numbers for a few parts that were listed under Mouser part no's
2025-12-09 add --nightmode option to command line config tool
2025-12-10 exp board: BOM de-mousering
2025-12-10 Addressed typo: changed 'uknown' to 'unknown'
2025-12-10 Improved clarity by fixing typo: 'buliding' corrected to 'building'
2025-12-10 Corrected a spelling mistake: 'buliding' → 'building'
2025-12-10 Improved clarity by fixing typo: 'satify' corrected to 'satisfy'
2025-12-10 Addressed typo: changed 'dyanmic' to 'dynamic'
2025-12-10 Fixed typo in documentation/code: 'uknown' was replaced with 'unknown'
2025-12-10 Resolved a minor textual error by changing 'desciptor' to 'descriptor'
2025-12-10 Resolved a minor textual error by changing 'statics' to 'statistics'
2025-12-10 Corrected a spelling mistake: 'statics' → 'statistics'
2025-12-10 Addressed typo: changed 'immediatly' to 'immediately'
2025-12-10 Resolved a minor textual error by changing 'reecord' to 'record'
2025-12-10 Addressed typo: changed 'funtion' to 'function'
2025-12-10 Improved clarity by fixing typo: 'statics' corrected to 'statistics'
2025-12-10 Improved clarity by fixing typo: 'muliplying' corrected to 'multiplying'
2025-12-10 Corrected a spelling mistake: 'trasnfer' → 'transfer'
2025-12-10 Corrected a spelling mistake: 'successul' → 'successful'
2025-12-10 Improved clarity by fixing typo: 'noticable' corrected to 'noticeable'
2025-12-10 Resolved a minor textual error by changing 'alerady' to 'already'
2025-12-10 Corrected a spelling mistake: 'requirments' → 'requirements'
2025-12-10 Improved clarity by fixing typo: 'alerady' corrected to 'already'
2026-01-21 explicitly exclude SDK stdio (messes with GP0/GP1 for PIO usage); allow 74hc595.enable to be undefined
2026-01-21 v1.0.1
2026-01-21 fix 'chain' error check in 74hc165 button setup
2026-01-30 fix error message string template in PWMWorker
2026-01-30 cmakelists comments
2026-01-30 Config tool JSON editor: click on Call Tip to go to help section; dismiss auto-complete when hitting ':' at end of property name
2026-02-01 KL25Z adapter JSON - comment edits
2026-02-07 add TCL/JVC IR protocol support (used by some TCL TVs and older JVC products)
2026-02-07 Exp Boards: KL25Z adapter: JSON config: set 74HC595 /ENA port to inverted logic (output is inverted in hardware on Pinscape KL25Z expansion board)
2026-02-10 output tester window: scroll control into view if necessary when using keyboard navigation (tab/shift+tab)
2026-02-11 config tool: add On/Off buttons alongside output port sliders
2026-02-12 config tool: plunger viewer tweaks
2026-03-16 comment/string typo cleanup (courtesy of Monstertov)
2026-03-16 config tool: output tester: ON/OFF toggle button saves last ON level
2026-03-16 DIY expansion board config template: fix old comment about PCA9555 button inputs (issue #100)
2026-03-23 Config Ref edits
2026-04-29 Fix logging message in PWMWorker
2026-04-29 Fix menu enabling status for a couple of extra device commands when device isn't present
2026-04-29 RP2350 build: override UF2 builder step to OMIT --abs-block (clobbers file system root table if enabled)
2026-04-29 New Pin Cab Input whitepaper typo
2026-04-30 Add optional MacOS-compatible usage for feedback controller HID, using vendor usage page space
2026-05-01 fix build error (board type set wrong in uf2 generator)
2026-05-01 build fix (uf2 type issue - really fix it this time)
